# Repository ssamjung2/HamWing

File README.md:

# HamWing
A FeatherWing for Dorji DRA818V/U modules that is compatible with Adafruit Feather system.

## HamWing Board Images

Front board render:

Back board render:

Full board view:

Additional board views:

The HamWing FeatherWing allows you to create a fully functional VHF/UHF transceiver using the Adafruit Feather platform. It has the same physical dimensions as the Feather Tripler making it easy to add a microcontroller as well as other FeatherWings like an OLED for a display. The modules are powered via the BAT pin to allow use with a LiPo pack connected to the Feather used for control. The HamWing was designed around the use of an Adafruit Feather M0 but should be compatible with other Feathers as well. We will list other compatible boards as they are verified to work.

The HamWIng can be built as a single band transceiver by populating only one RF module, low pass filter components and u.FL connector.

A 4 pin TRRS jack is used for a speaker mic with PTT button. A LM4810 amplifier is used for audio out. Mic input is shared with both modules. The PTT line is connected to a GPIO pin for use in keying the DRA818 module(s). Configuration of the modules is accomplished using AT commands via serial UART connected to each. The VHF module uses the default serail UART. The UHF module uses a second serial UART created using a SERCOM. This should also work on other Feathers using Software Serial.

Ouput of the modules is connected to a low pass filter to supress harmonics before being routed to a u.FL connector for each.

This project uses the following license for hardware, software and documentation.

## DRA818 Pin And Signal Assignments (From KiCad Project)

The tables below are derived from `KiCad/FeatherWing_KC5.kicad_pcb` and cross-checked with `KiCad/FeatherWing_KC5.sch`.

### DRA818 Pins Quick Reference

U1 is the VHF module position (DRA818V) and U2 is the UHF module position (DRA818U).

| DRA818 Pad | Board-Level Function |
|---|---|
| 8 | VBAT supply input |
| 9, 10 | Ground |
| 12 | RF output into LPF and then u.FL connector |
| 16, 17 | UART/control serial path (direct on U1, jumper-routed on U2) |
| 6, 7 | Shared control lines (JP4-selectable + common A4 line) |
| 18 | Shared audio/control node tied to C9 network |

For full per-pad net assignments for both modules, use the complete table below.

### DRA818 Module Pad Mapping

| DRA818 Pad | U1 (DRA818V) Assignment | U2 (DRA818U) Assignment | Notes |
|---|---|---|---|
| 1 | A0 | A1 | Feather GPIO/analog control lines |
| 2 | Net-(U1-Pad2) | Net-(U2-Pad2) | Internal module signal (not named in schematic) |
| 3 | Net-(C5-Pad1) | Net-(C6-Pad1) | Coupled through C5/C6 into audio chain |
| 4 | Net-(U1-Pad4) | Net-(U2-Pad4) | Internal module signal (not named in schematic) |
| 5 | A2 | A3 | Feather GPIO/analog control lines |
| 6 | Net-(JP4-Pad1) | Net-(JP4-Pad1) | Shared control line, jumper-selectable to F5 |
| 7 | A4 | A4 | Shared control line to both modules |
| 8 | VBAT | VBAT | Module supply from Feather battery rail |
| 9 | GND | GND | Ground |
| 10 | GND | GND | Ground |
| 11 | Net-(U1-Pad11) | Net-(U2-Pad11) | Internal module signal (not named in schematic) |
| 12 | Net-(L3-Pad2) | Net-(L6-Pad2) | RF output path into LPF network and u.FL |
| 13 | Net-(U1-Pad13) | Net-(U2-Pad13) | Internal module signal (not named in schematic) |
| 14 | Net-(U1-Pad14) | Net-(U2-Pad14) | Internal module signal (not named in schematic) |
| 15 | Net-(U1-Pad15) | Net-(U2-Pad15) | Internal module signal (not named in schematic) |
| 16 | TX | Net-(JP2-Pad2) | U1 on Feather UART TX; U2 via JP2 to F3 |
| 17 | RX | Net-(JP1-Pad2) | U1 on Feather UART RX; U2 via JP1 to F4 |
| 18 | Net-(C9-Pad2) | Net-(C9-Pad2) | Shared AC-coupled/bias audio/control input node |

### Feather Header And Jumper Routing

| Board Signal | Source | Destination |
|---|---|---|
| TX | Feather J1 pin 2 | U1 pad 16 |
| RX | Feather J1 pin 3 | U1 pad 17 |
| F3 | Feather J2 pin 6 | JP2 pad 1 (bridge to U2 pad 16 when closed) |
| F4 | Feather J2 pin 7 | JP1 pad 1 (bridge to U2 pad 17 when closed) |
| F5 | Feather J2 pin 8 | JP4 pad 2 (bridge to shared U1/U2 pad 6 node when closed) |
| A5 | Feather J1 pin 7 | JP3 pad 2 (speaker-mic PTT route when closed) |

### Other Functional Connections

| Function | Connection Summary |
|---|---|
| VHF RF output | U1 pad 12 -> L3/L2/L1 LPF network -> J3 (u.FL) |
| UHF RF output | U2 pad 12 -> L6/L5/L4 LPF network -> J4 (u.FL) |
| Speaker-mic jack | J5 includes ground, PTT path, and shared mic/input path |
| Audio amp | U3 (LM4810) provides amplified audio output to the speaker-mic path |
| Shared mic/control bias | R4/C9 network ties J5 input path to shared U1/U2 pad 18 node |

### Notes

- Some DRA818 nets are unnamed in this project (`Net-(Ux-PadY)`). The board files identify routing, but not all module function names.
- To map every unnamed pad to official DRA818 pin function names, cross-reference these pad numbers with the DRA818 datasheet pinout.

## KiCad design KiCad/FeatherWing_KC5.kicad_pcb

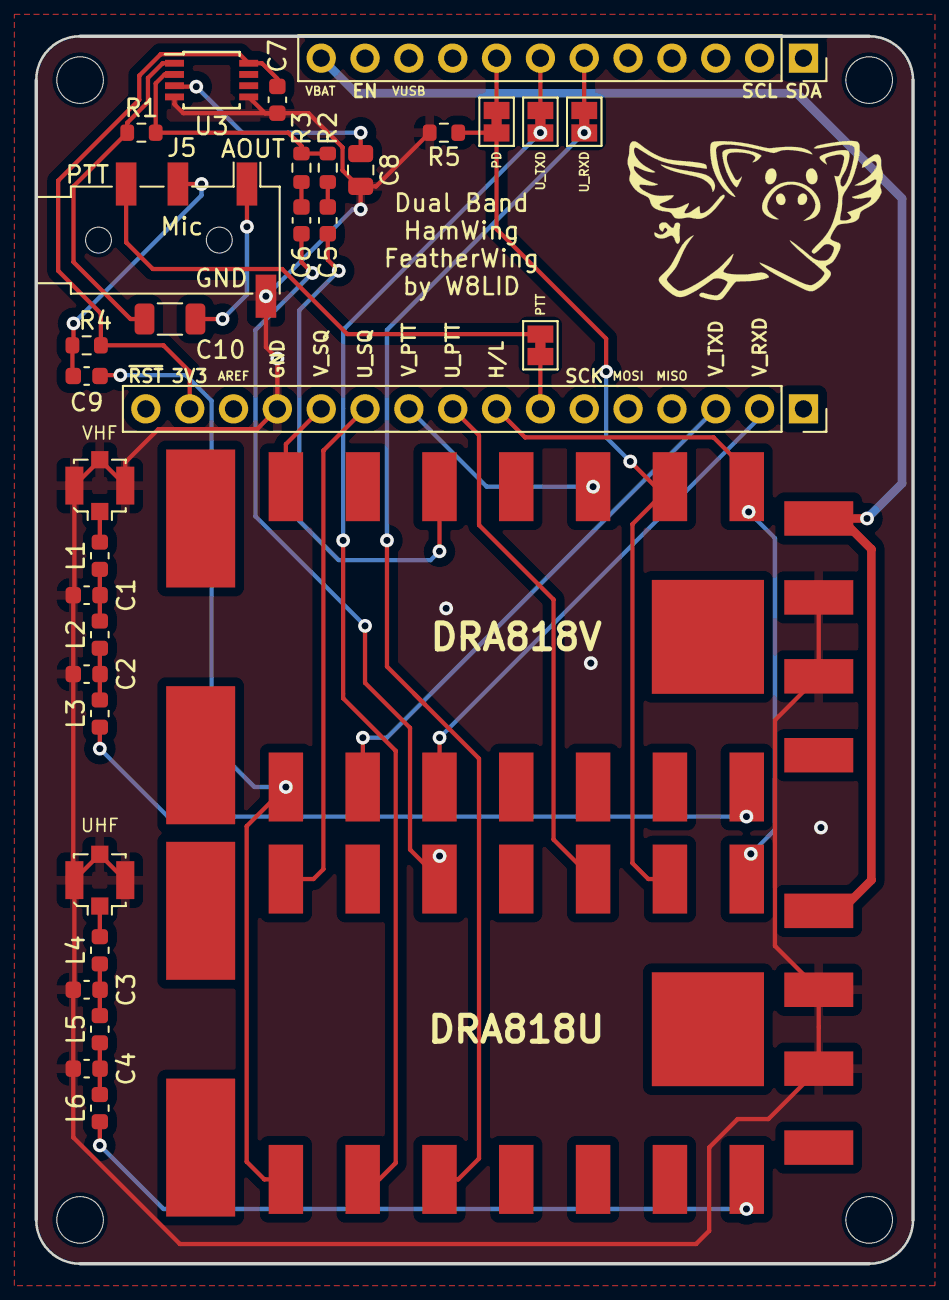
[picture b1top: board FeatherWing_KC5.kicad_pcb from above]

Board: 2 copper layers, 50.8 x 71.1 mm, 33 parts (0 on the bottom side), 36 nets.

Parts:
C1, C2: 27pF; C_0603_1608Metric
C3, C4: 8.7pF; C_0603_1608Metric
C5, C6: 0.47uF; C_0603_1608Metric
C7: 1uF; C_0603_1608Metric
C8: 4.7uF; C_0805_2012Metric
C9: 100nF; C_0603_1608Metric
C10: 100uF; C_1206_3216Metric
J1: feather long; PinSocket_1x16_P2.54mm_Vertical
J2: feather short; PinSocket_1x12_P2.54mm_Vertical
J5: AudioJack4; Jack_3.5mm_PJ320D_Horizontal
JP1, JP2, JP3: Jumper_2_Bridged; SolderJumper-2_P1.3mm_Bridged_Pad1.0x1.5mm
L1, L3: 56nH; L_0603_1608Metric
L2: 100nH; L_0603_1608Metric
L4, L6: 18nH; L_0603_1608Metric
L5: 30nH; L_0603_1608Metric
PD: Jumper_2_Bridged; SolderJumper-2_P1.3mm_Bridged_Pad1.0x1.5mm
R1, R2, R3: 20k; R_0603_1608Metric
R4, R5: 10k; R_0603_1608Metric
U1: DRA818V; DRA818
U2: DRA818U; DRA818
U3: LM4810; TSSOP-8_3x3mm_P0.65mm
UHF: Conn_Coaxial; U.FL_Molex_MCRF_73412-0110_Vertical
VHF: Conn_Coaxial; U.FL_Molex_MCRF_73412-0110_Vertical

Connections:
+3V3: C7.2, J1.15, R4.2, U3.8
/A0: J1.12, U1.1
/A1: J1.11, U2.1
/A2: J1.10, U1.5
/A3: J1.9, U2.5
/A4: J1.8, U1.7, U2.7
/A5: J1.7, JP3.2
/F3: J2.6, JP2.1
/F4: J2.7, JP1.1
/F5: J2.8, PD.2
/RX: J1.3, U1.17
/TX: J1.2, U1.16
/VBAT: J2.12, U1.8, U2.8
GND: C1.2, C2.2, C3.2, C4.2, C7.1, C8.2, J1.13, J5.S, R5.1, U1.9, U1.10, U2.9, U2.10, U3.4, U3.5, UHF.2, VHF.2
unnamed: C1.1, L1.2, L2.1
unnamed: C2.1, L2.2, L3.1
unnamed: C3.1, L4.2, L5.1
unnamed: C4.1, L5.2, L6.1
unnamed: C5.1, U1.3
unnamed: C5.2, R2.1
unnamed: C6.1, U2.3
unnamed: C6.2, R3.2
unnamed: C8.1, U3.3
unnamed: C9.1, J5.R1, R4.1
unnamed: C9.2, U1.18, U2.18
unnamed: C10.1, J5.T
unnamed: C10.2, R1.1, U3.1
unnamed: L1.1, VHF.1
unnamed: L4.1, UHF.1
unnamed: J5.R2, JP3.1
unnamed: JP1.2, U2.17
unnamed: JP2.2, U2.16
unnamed: PD.1, R5.2, U1.6, U2.6
unnamed: L3.2, U1.12
unnamed: L6.2, U2.12
unnamed: R1.2, R2.2, R3.1, U3.2

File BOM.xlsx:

Referance | Value | Footprint | LCSC P/N | Digi-Key P/N
L1, L3 | 56nH | 0603 | C316308
L2 | 97nH (100nH) | 0603 |  | 445-6386-1-ND
L4, L6 | 18nH | 0603 | C316321
L5 | 31nH (30nH) | 0603 |  | 490-6883-1-ND
C1,2 | 27pF | 0603 | C342893
C3,4 | 8.7pF | 0603 |  | 490-17287-1-ND
C5,6 | 0.47uF | 0603 |  | 732-7912-1-ND
C7 | 1uF | 0603 | C26413
C8 | 4.7uF | 0805 | C215908
C9 | 100nF | 0603 | C42998
C10 | 100uF | 1206 | C77085
R1,2,3 | 20k | 0603 | C160027
R4,5 | 10k | 0603 | C269701
J1 | 1x16 Pin | 2.54mm
J2 | 1x12 Pin | 2.54mm
J3,4 | u.FL |  | C88374
J5 | PJ320D
U1 | DRA818V
U2 | DRA818U
U3 | LM4810 | SSOP8 |  | LM4810MM/NOPBCT-ND

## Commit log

2026-03-22 KiCad Updates
    Imported project to KiCad 8.0
2026-03-22 Latest updates and renders
    Imported project to KiCad 8.0
2026-03-22 Add KiCad 8.0 import and new renders section
    Imported project into KiCad 8.0 and updated renders.
